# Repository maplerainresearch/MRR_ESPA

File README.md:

# MRR ESPA
## A basic 3D printer control board based on ESP32

This is a bare-minimum 3D printer control board based on the ESP32 microcontroller, which comes with built-in WiFi and BlueTooth.

Current version: v1.3

Get a pre-launch version at our [store](https://www.maplerain.com/en/products).

Facebook [page](https://www.facebook.com/mrrespx/) <br>
Facebook [group](https://www.facebook.com/groups/mrr.espx.users/) (for discussions, etc.)

## Features:
- Able to use up to 4 stepper drivers: X, Y, Z, and E0
- 12V to 24V input power supply
- Separate power supply for the heat bed
- X, Y, and Z min endstops
- Allows the use of a Z-axis probe, such as an inductive sensor, running on the input supply voltage (12V to 24V)
- AUX1 connector for use with an external host, such as the closed-source MKS TFT32 (**Untested!!**)
- Physical size of 99.5mm by 90.5mm. Mounting holes are 3.5mm in diameter, with centers 4mm from the edges.
- "RESET" button can be used to reset the board.

Check out the [Kickstarter page.](https://www.kickstarter.com/projects/maplerainresearch/mrr-espa)

# Firmware

Marlin 2.0 has added support for ESP32. This board was based on the initial pins definition used. <br>
In addition, [Luc](https://github.com/luc-github) has been working on a Marlin fork which incorporates part of his ESP3D webUI into Marlin itself.

## Flashing firmware

- You should be able to flash firmware through the USB port. Depending on your operating system, you may need to install drivers for the CH340. Please use Google or another search engine to find the right CH340 driver for your operating system.
- To flash firmware by directly connecting to TX/RX pins, you will need to connect IO0 to GND, then reboot (press "BOOT" button) to enter flash mode. After flashing the firmware, disconnect IO0 from GND, and press "BOOT" button again to reboot into normal mode.
- Use a baud rate of 115200.
- Once the firmware has been flashed for the first time, further updates can be flashed via OTA.

# Jumpers

- 5V_SEL: Connect to VIN for normal operation; only short (close) this jumper to VUSB if you need to power the board via USB. Note: Powering the board with both PSU and USB may cause unstable operation during heating.
- PWR_SEL: Connect the middle pin PWR_SEL to pin labeled "12V" if using 12V; connect PWR_SEL to pin labeled "24V" if using 24V.
- Stepper driver jumpers:
  - MS1: VIO to set high; SPI if using TMC SPI mode
  - MS2: VIO to set high; SPI if using TMC SPI mode
  - MS3: VIO to set high; SPI if using TMC SPI mode
  - RST: SLP if using A4988/DRV8825; SPI if using TMC SPI mode

# Pins

See separate PIN_DEF.txt file.

# License
Released under CERN Open Hardware Licence v1.2. See LICENSE.txt for details.

## Warning

- This product uses high currents which may cause fires. Use with caution.
- Do not use input voltages higher than 24V. Input current must not exceed 15A.
- Do not attempt to use more than 15A for the heated bed. While the MOSFET is capable of such currents, the connectors are not. If you need more than 15A, use an external MOSFET. In any case, it is highly recommended to use an external MOSFET for the heated bed to avoid drawing high currents through this product.
- If using a current of more than 10A for the heated bed, it is highly recommended to provide active cooling for the board as the MOSFET and adjacent areas can get very hot due to the high current.
- The underside of the board has PCB traces which are exposed for better cooling. These traces may be carrying high currents and can get very hot. DO NOT touch them, and DO NOT allow these traces to come into contact with metal or other conductive materials.
- Do not attempt to use more than 5A for the hot end. While the MOSFET is capable of such currents, the connectors are not. If you need more than 5A, use an external MOSFET.
- Do not reverse polarity.
- The breakout and endstop pins are rated for 3.3V, which is the voltage the ESP32 operates at. Attempting to feed inputs above 3.3V to these pins may damage the board.
- It is recommended to power the board only via USB (i.e. turn off PSU power supply) when flashing the board.

## Disclaimer

This product is provided as-is. While care has been taken to design a safe product, it is the user's responsibility to make sure precautions are taken to prevent damage or injury when using this product. This includes adhering to all warnings provided. By using this product, the user accepts responsibility to bear all liabilities from any damage or injury arising from the use of this product.

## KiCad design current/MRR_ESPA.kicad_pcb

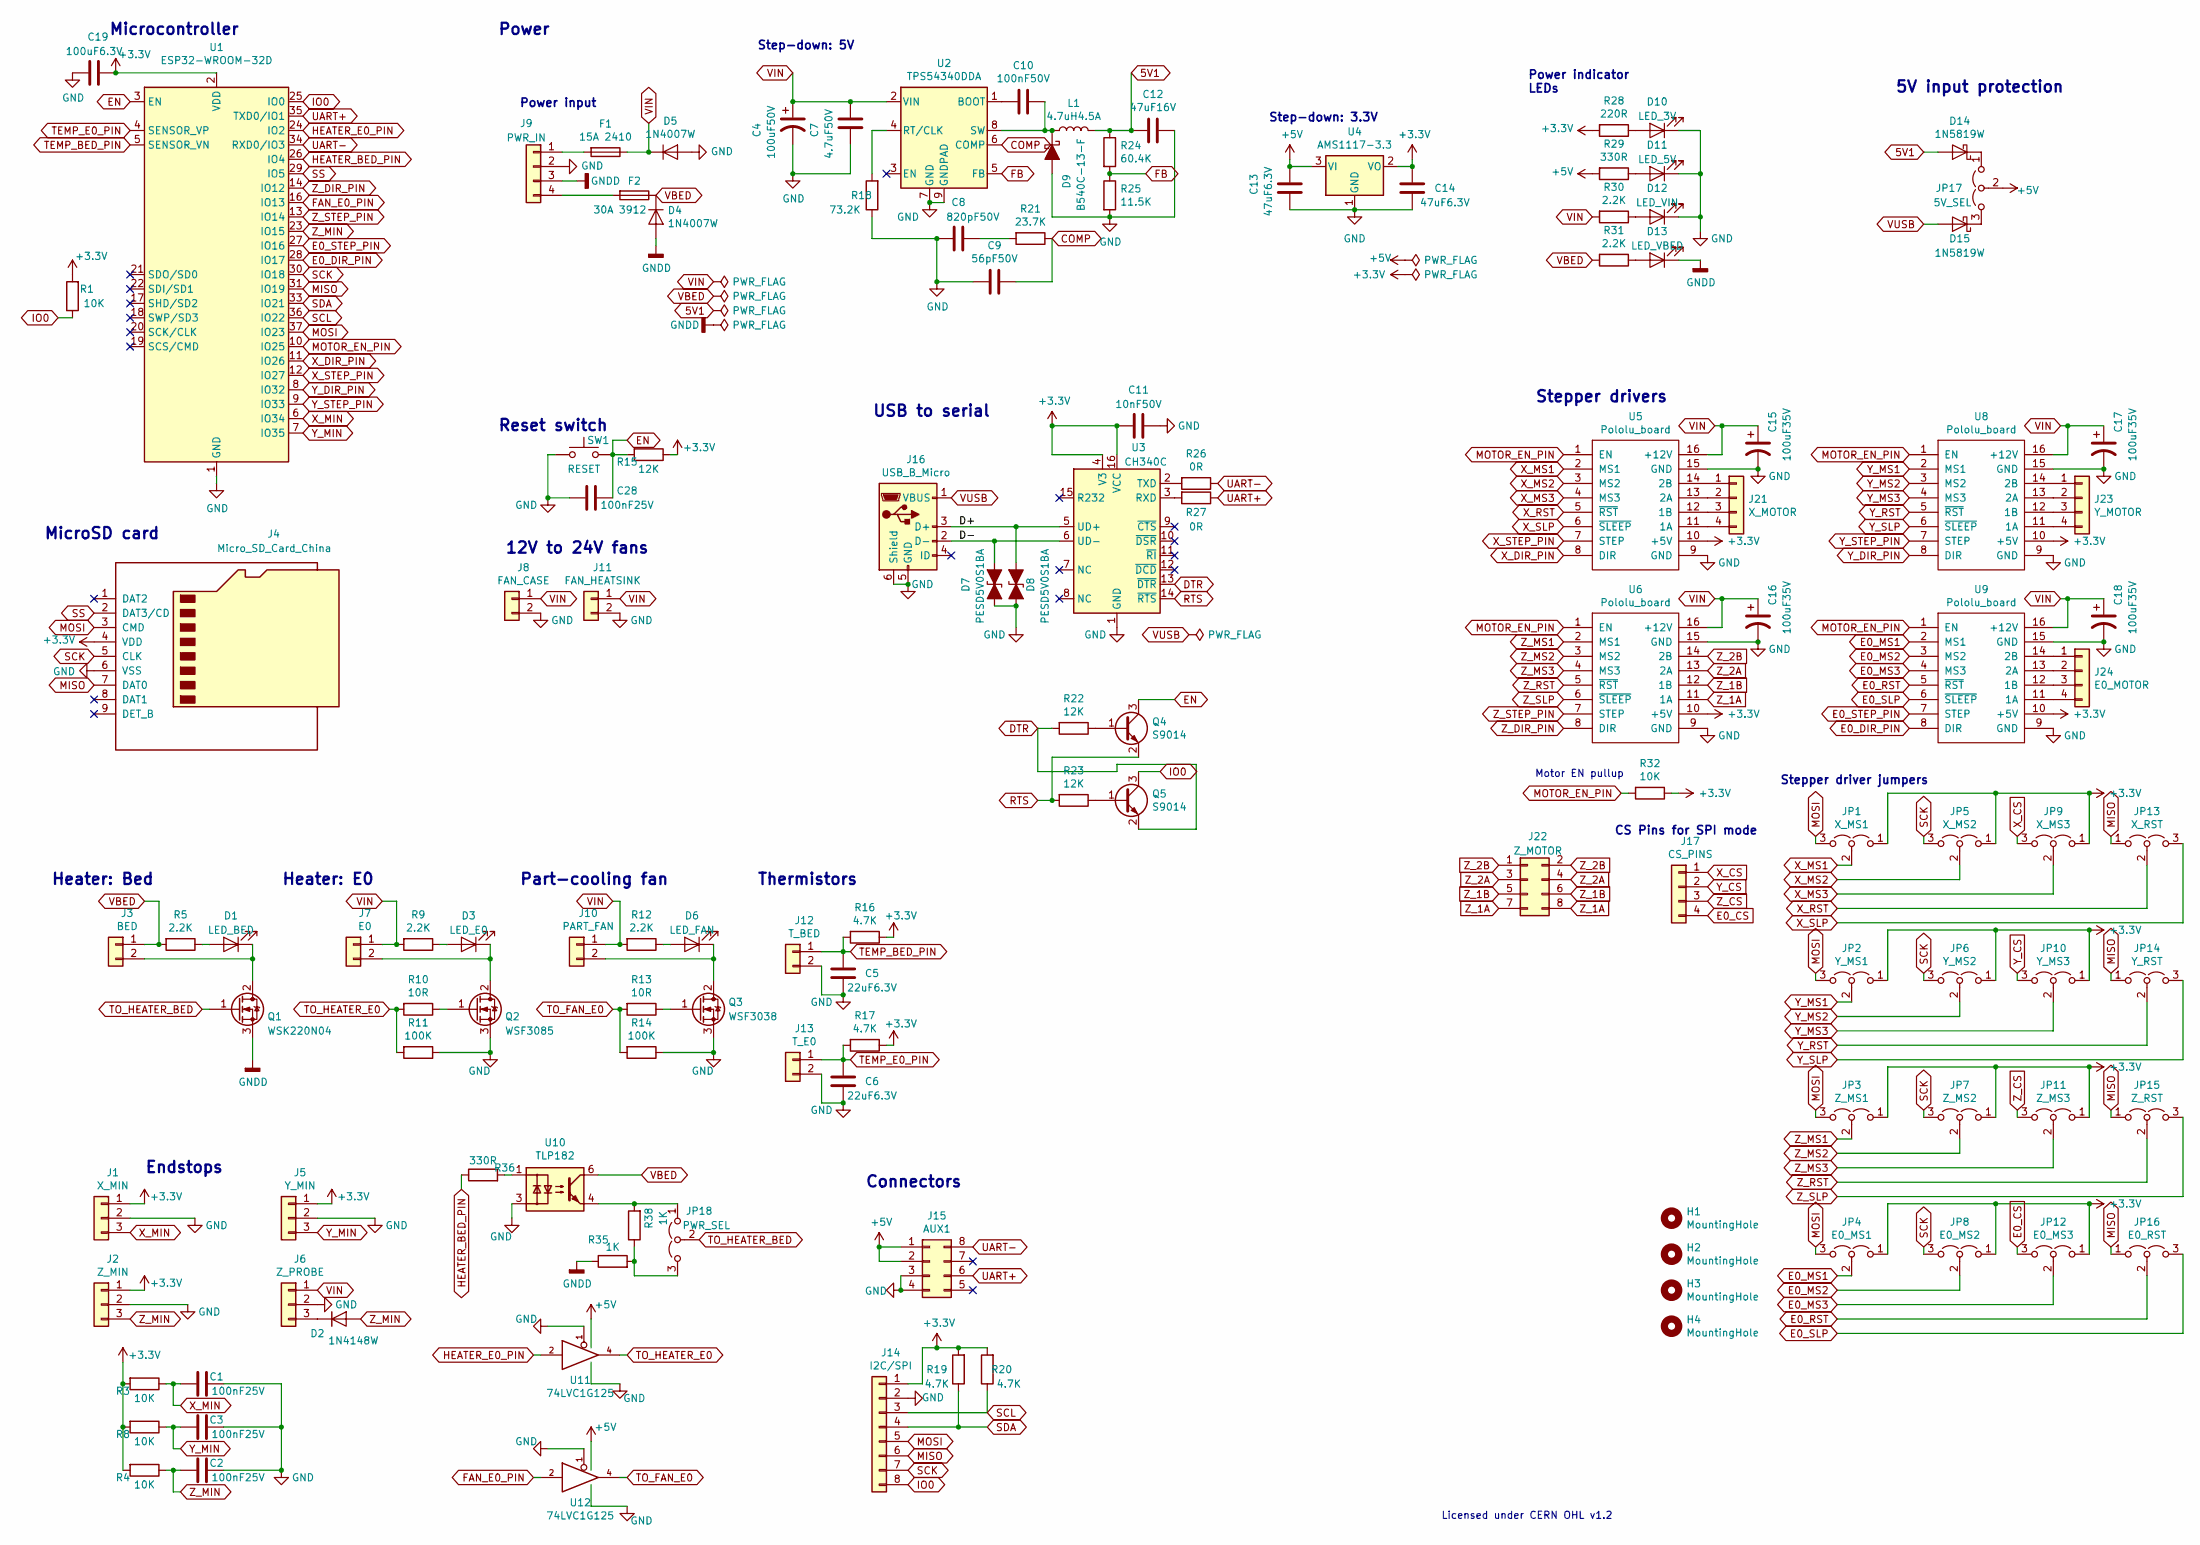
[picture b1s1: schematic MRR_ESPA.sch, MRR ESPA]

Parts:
C1, C2, C3, C28: 100nF25V; C_0805_2012Metric; Mfg part no. 0805B104K250; LCSC Part Number C128353
C4: 100uF50V; CP_Elec_8x10; Mfg part no. VEJ101M1HTR-0810; LCSC Part Number C176665
C5, C6: 22uF6.3V; C_0805_2012Metric; Mfg part no. CL21A226MQQNNNE; LCSC Part Number C5674
C7: 4.7uF50V; C_1206_3216Metric; Mfg part no. CL31B475KBHNFNE; LCSC Part Number C307575
C8: 820pF50V; C_0805_2012Metric; Mfg part no. 0805B821K500CT; LCSC Part Number C152862
C9: 56pF50V; C_0805_2012Metric; Mfg part no. 0805N560J500CT; LCSC Part Number C296102
C10: 100nF50V; C_0805_2012Metric; Mfg part no. GCM21BR71H104KA37L; LCSC Part Number C161260
C11: 10nF50V; C_0805_2012Metric; Mfg part no. 0805B103K500NT; LCSC Part Number C52278
C12: 47uF16V; C_1206_3216Metric; Mfg part no. LMK316BJ476ML-T; LCSC Part Number C92821
C13, C14: 47uF6.3V; C_0805_2012Metric; Mfg part no. JMK212BJ476MG-T; LCSC Part Number C87159
C15, C16, C17, C18: 100uF35V; CP_Elec_6.3x7.7; Mfg part no. CS1V101M-CRE77; LCSC Part Number C97811
C19: 100uF6.3V; C_1206_3216Metric; Mfg part no. CL31A107MQHNNNE; LCSC Part Number C15008
D1: LED_BED; LED_0805; Mfg part no. 17-21SURC/S530-A3/TR8; LCSC Part Number C72037
D2: 1N4148W; D_SOD-123; Mfg part no. 1N4148W; LCSC Part Number C81598
D3: LED_E0; LED_0805; Mfg part no. 17-21SURC/S530-A3/TR8; LCSC Part Number C72037
D4, D5: 1N4007W; D_SOD-123F; Mfg part no. 1N4007W; LCSC Part Number C108803
D6: LED_FAN; LED_0805; Mfg part no. 17-21SURC/S530-A3/TR8; LCSC Part Number C72037
D7, D8: PESD5V0S1BA; D_SOD-323; Mfg part no. PESD5V0S1BA,115; LCSC Part Number C19224
D9: B540C-13-F; D_SMC; Mfg part no. B540C-13-F; LCSC Part Number C72264
D10: LED_3V; LED_0805; Mfg part no. 17-21SYGC/S530-E2/TR8; LCSC Part Number C73548
D11: LED_5V; LED_0805; Mfg part no. 17-21SYGC/S530-E2/TR8; LCSC Part Number C73548
D12: LED_VIN; LED_0805; Mfg part no. 17-21/BHC-XL2M2TY/3T; LCSC Part Number C72035
D13: LED_VBED; LED_0805; Mfg part no. 17-21/BHC-XL2M2TY/3T; LCSC Part Number C72035
D14, D15: 1N5819W; D_SOD-123; Mfg part no. 1N5819W; LCSC Part Number C169540
F1: 15A 2410; Littelfuse_0451; Mfg part no. 0451015.MRL; LCSC Part Number C44480
F2: 30A 3912; Littelfuse_456; Mfg part no. 0456030.ER; LCSC Part Number C187558
H1, H2, H3, H4: MountingHole; MountingHole_3.2mm_M3_DIN965
J1: X_MIN; JST_XH_B03B-XH-A_1x03_P2.50mm_Vertical; Mfg part no. B3B-XH-A(LF)(SN); LCSC Part Number C144394
J2: Z_MIN; JST_XH_B03B-XH-A_1x03_P2.50mm_Vertical; Mfg part no. B3B-XH-A(LF)(SN); LCSC Part Number C144394
J3: BED; TerminalBlock_Phoenix_MKDS-3-2-5.08_1x02_P5.08mm_Horizontal; Mfg part no. MKDS3/2-5.08; LCSC Part Number C89120
J4: Micro_SD_Card_China; Conn_uSDcard; Mfg part no. TF-15×15; LCSC Part Number C111196
J5: Y_MIN; JST_XH_B03B-XH-A_1x03_P2.50mm_Vertical; Mfg part no. B3B-XH-A(LF)(SN); LCSC Part Number C144394
J6: Z_PROBE; JST_XH_B03B-XH-A_1x03_P2.50mm_Vertical; Mfg part no. B3B-XH-A(LF)(SN); LCSC Part Number C144394
J7: E0; TerminalBlock_Phoenix_MKDS-1,5-2-5.08_1x02_P5.08mm_Horizont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; Mfg part no. MKDSN1.5/2-5.08; LCSC Part Number C91153
J8: FAN_CASE; PinHeader_1x02_P2.54mm_Vertical; Mfg part no. C124375; LCSC Part Number C124375
J9: PWR_IN; TerminalBlock_Phoenix_MKDS-3-4-5.08_1x04_P5.08mm_Horizontal; Mfg part no. MKDS3/4-5.08; LCSC Part Number C90087
J10: PART_FAN; PinHeader_1x02_P2.54mm_Vertical; Mfg part no. C124375; LCSC Part Number C124375
J11: FAN_HEATSINK; PinHeader_1x02_P2.54mm_Vertical; Mfg part no. C124375; LCSC Part Number C124375
J12: T_BED; JST_XH_B02B-XH-A_1x02_P2.50mm_Vertical; Mfg part no. B2B-XH-A(LF)(SN); LCSC Part Number C158012
J13: T_E0; JST_XH_B02B-XH-A_1x02_P2.50mm_Vertical; Mfg part no. B2B-XH-A(LF)(SN); LCSC Part Number C158012
J14: I2C/SPI; PinHeader_1x08_P2.54mm_Vertical; Mfg part no. C124381; LCSC Part Number C124381
J15: AUX1; IDC-Header_2x04_P2.54mm_Vertical; Mfg part no. C9135; LCSC Part Number C9135
J16: USB_B_Micro; USB_Micro-B_Molex-105017-0001; Mfg part no. 105017-0001; LCSC Part Number C136000
J17: CS_PINS; PinHeader_1x04_P2.54mm_Vertical; Mfg part no. C124378; LCSC Part Number C124378
J21: X_MOTOR; PinHeader_1x04_P2.54mm_Vertical; Mfg part no. C124378; LCSC Part Number C124378
J22: Z_MOTOR; PinHeader_2x04_P2.54mm_Vertical; Mfg part no. C124386; LCSC Part Number C124386
J23: Y_MOTOR; PinHeader_1x04_P2.54mm_Vertical; Mfg part no. C124378; LCSC Part Number C124378
J24: E0_MOTOR; PinHeader_1x04_P2.54mm_Vertical; Mfg part no. C124378; LCSC Part Number C124378
JP1: X_MS1; PinHeader_1x03_P2.54mm_Vertical; Mfg part no. C124376; LCSC Part Number C124376
JP2: Y_MS1; PinHeader_1x03_P2.54mm_Vertical; Mfg part no. C124376; LCSC Part Number C124376
JP3: Z_MS1; PinHeader_1x03_P2.54mm_Vertical; Mfg part no. C124376; LCSC Part Number C124376
JP4: E0_MS1; PinHeader_1x03_P2.54mm_Vertical; Mfg part no. C124376; LCSC Part Number C124376
JP5: X_MS2; PinHeader_1x03_P2.54mm_Vertical; Mfg part no. C124376; LCSC Part Number C124376
JP6: Y_MS2; PinHeader_1x03_P2.54mm_Vertical; Mfg part no. C124376; LCSC Part Number C124376
JP7: Z_MS2; PinHeader_1x03_P2.54mm_Vertical; Mfg part no. C124376; LCSC Part Number C124376
JP8: E0_MS2; PinHeader_1x03_P2.54mm_Vertical; Mfg part no. C124376; LCSC Part Number C124376
JP9: X_MS3; PinHeader_1x03_P2.54mm_Vertical; Mfg part no. C124376; LCSC Part Number C124376
JP10: Y_MS3; PinHeader_1x03_P2.54mm_Vertical; Mfg part no. C124376; LCSC Part Number C124376
JP11: Z_MS3; PinHeader_1x03_P2.54mm_Vertical; Mfg part no. C124376; LCSC Part Number C124376
JP12: E0_MS3; PinHeader_1x03_P2.54mm_Vertical; Mfg part no. C124376; LCSC Part Number C124376
JP13: X_RST; PinHeader_1x03_P2.54mm_Vertical; Mfg part no. C124376; LCSC Part Number C124376
JP14: Y_RST; PinHeader_1x03_P2.54mm_Vertical; Mfg part no. C124376; LCSC Part Number C124376
JP15: Z_RST; PinHeader_1x03_P2.54mm_Vertical; Mfg part no. C124376; LCSC Part Number C124376
JP16: E0_RST; PinHeader_1x03_P2.54mm_Vertical; Mfg part no. C124376; LCSC Part Number C124376
JP17: 5V_SEL; PinHeader_1x03_P2.54mm_Vertical; Mfg part no. C124376; LCSC Part Number C124376
JP18: PWR_SEL; PinHeader_1x03_P2.54mm_Vertical; Mfg part no. C124376; LCSC Part Number C124376
L1: 4.7uH4.5A; SMMS0530; Mfg part no. SMMS0530-4R7M; LCSC Part Number C181722
Q1: WSK220N04; TO-263-2; Mfg part no. WSK220N04; LCSC Part Number C148446
Q2: WSF3085; TO-252-2; Mfg part no. WSF3085; LCSC Part Number C148428
Q3: WSF3038; TO-252-2; Mfg part no. WSF3038; LCSC Part Number C148426
Q4, Q5: S9014; SOT-23; Mfg part no. S9014; LCSC Part Number C181164
R1, R3, R4, R8, R32: 10K; R_0805_2012Metric; Mfg part no. 0805W8F2201T5E; LCSC Part Number C38522
R5, R9, R12, R30, R31: 2.2K; R_0805_2012Metric; Mfg part no. 0805W8F2201T5E; LCSC Part Number C17520
R10, R13: 10R; R_0805_2012Metric; Mfg part no. 0805W8F100JT5E; LCSC Part Number C17415
R11, R14: 100K; R_0805_2012Metric; Mfg part no. 0805W8F1003T5E; LCSC Part Number C149504
R15, R22, R23: 12K; R_0805_2012Metric; Mfg part no. 0805W8F1202T5E; LCSC Part Number C17444
R16, R17, R19, R20: 4.7K; R_0805_2012Metric; Mfg part no. 0805W8F4701T5E; LCSC Part Number C17673
R18: 73.2K; R_0805_2012Metric; Mfg part no. WR08X7322FTL; LCSC Part Number C170958
R21: 23.7K; R_0805_2012Metric; Mfg part no. WR08X2372FTL; LCSC Part Number C170848
R24: 60.4K; R_0805_2012Metric; Mfg part no. RC0805FR-0760K4L; LCSC Part Number C273994
R25: 11.5K; R_0805_2012Metric; Mfg part no. 0805W8F1152T5E; LCSC Part Number C17418
R26, R27: 0R; R_0805_2012Metric; Mfg part no. 0805W8F0000T5E; LCSC Part Number C17477
R28: 220R; R_0805_2012Metric; Mfg part no. 0805W8F2200T5E; LCSC Part Number C17557
R29, R36: 330R; R_0805_2012Metric; Mfg part no. 0805W8F3300T5E; LCSC Part Number C17630
R35, R38: 1K; R_0805_2012Metric; Mfg part no. 0805W8F1001T5E; LCSC Part Number C17513
SW1: RESET; 6x6mmTactileSwitch; Mfg part no. K2-6639SP-C4SC-04; LCSC Part Number C83206
U1: ESP32-WROOM-32D; ESP32-WROOM-32; Mfg part no. ESP32-WROOM-32; LCSC Part Number C95209
U2: TPS54340DDA; TI_SO-PowerPAD-8_ThermalVias; Mfg part no. TPS54340DDAR; LCSC Part Number C45886
U3: CH340C; SOIC-16_3.9x9.9mm_P1.27mm; Mfg part no. CH340C; LCSC Part Number C84681
U4: AMS1117-3.3; SOT-223-3_TabPin2; Mfg part no. AMS1117-3.3; LCSC Part Number C6186
U5, U6, U8, U9: Pololu_board; Pololu_Breakout-16_15.2x20.3mm; Mfg part no. x2; LCSC Part Number C27438
U10: TLP182; MFSOP6-4_4.4x3.6mm_P1.27mm; Mfg part no. TLP182(GB-TPL,E; LCSC Part Number C96457
U11, U12: 74LVC1G125; SOT-353_SC-70-5; Mfg part no. 74LVC1G125GW,125; LCSC Part Number C12519

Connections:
5V1: C12.2, D14.2 (A), L1.2, R24.1
+3V3: C11.2, C14.1, C19.1, J1.1, J2.1, J4.4 (VDD), J5.1, J14.1, JP1.1 (A), JP2.1 (A), JP3.1 (A), JP4.1 (A), JP5.1 (A), JP6.1 (A), JP7.1 (A), JP8.1 (A), JP9.1 (A), JP10.1 (A), JP11.1 (A), JP12.1 (A), R1.2, R3.2, R4.2, R8.2, R15.1, R16.1, R17.1, R19.2, R20.2, R28.2, R32.1, U1.2 (VDD), U3.4 (V3), U3.16 (VCC), U4.2 (VO), U5.10 (+5V), U6.10 (+5V), U8.10 (+5V), U9.10 (+5V)
+5V: C13.1, J15.1, J15.2, JP17.2 (C), R29.2, U4.3 (VI), U11.5 (VCC), U12.5 (VCC)
/D+: D8.1 (A1), J16.3 (D+), U3.5 (UD+)
/D-: D7.1 (A1), J16.2 (D-), U3.6 (UD-)
COMP: C9.1, R21.1, U2.6 (COMP)
DTR: Q5.2 (E), R22.2, U3.13 (~DTR)
E0_CS: J17.4, JP12.3 (B)
E0_DIR_PIN: U1.28 (IO17), U9.8 (DIR)
E0_MS1: JP4.2 (C), U9.2 (MS1)
E0_MS2: JP8.2 (C), U9.3 (MS2)
E0_MS3: JP12.2 (C), U9.4 (MS3)
E0_RST: JP16.2 (C), U9.5 (~RST)
E0_SLP: JP16.3 (B), U9.6 (~SLEEP)
E0_STEP_PIN: U1.27 (IO16), U9.7 (STEP)
EN: C28.1, Q4.3 (C), R15.2, SW1.2, U1.3 (EN)
FAN_E0_PIN: U1.16 (IO13), U12.2
FB: R24.2, R25.1, U2.5 (FB)
GND: C1.1, C2.1, C3.1, C4.2, C5.1, C6.1, C7.1, C8.2, C9.2, C11.1, C12.1, C13.2, C14.2, C15.2, C16.2, C17.2, C18.2, C19.2, C28.2, D5.2 (A), D7.2 (A2), D8.2 (A2), D9.2 (A), D10.1 (K), D11.1 (K), D12.1 (K), J1.2, J2.2, J4.6 (VSS), J5.2, J6.2, J8.2, J9.2, J11.2, J12.2, J13.2, J14.2, J15.3, J15.4, J16.5 (GND), J16.6 (Shield), Q2.3 (S), Q3.3 (S), R11.1, R14.1, R18.1, R25.2, SW1.1, U1.1 (GND), U1.15 (GND), U1.38 (GND), U1.39, U2.7 (GND), U2.9 (GNDPAD), U3.1 (GND), U4.1 (GND), U5.9 (GND), U5.15 (GND), U6.9 (GND), U6.15 (GND), U8.9 (GND), U8.15 (GND), U9.9 (GND), U9.15 (GND), U10.3, U11.1, U11.3 (GND), U12.1, U12.3 (GND)
GNDD: D4.2 (A), D13.1 (K), J9.3, Q1.3 (S), R35.1
HEATER_BED_PIN: R36.1, U1.26 (IO4)
HEATER_E0_PIN: U1.24 (IO2), U11.2
IO0: J14.8, Q5.3 (C), R1.1, U1.25 (IO0)
MISO: J4.7 (DAT0), J14.6, JP13.1 (A), JP14.1 (A), JP15.1 (A), JP16.1 (A), U1.31 (IO19)
MOSI: J4.3 (CMD), J14.5, JP1.3 (B), JP2.3 (B), JP3.3 (B), JP4.3 (B), U1.37 (IO23)
MOTOR_EN_PIN: R32.2, U1.10 (IO25), U5.1 (EN), U6.1 (EN), U8.1 (EN), U9.1 (EN)
unnamed: C8.1, R21.2
unnamed: C10.1, D9.1 (K), L1.1, U2.8 (SW)
unnamed: C10.2, U2.1 (BOOT)
unnamed: D1.1 (K), J3.2, Q1.2 (D)
unnamed: D1.2 (A), R5.1
unnamed: D2.1 (K), J6.3
unnamed: D3.1 (K), J7.2, Q2.2 (D)
unnamed: D3.2 (A), R9.1
unnamed: D6.1 (K), J10.2, Q3.2 (D)
unnamed: D6.2 (A), R12.1
unnamed: D10.2 (A), R28.1
unnamed: D11.2 (A), R29.1
unnamed: D12.2 (A), R30.1
unnamed: D13.2 (A), R31.1
unnamed: D14.1 (K), JP17.1 (A)
unnamed: D15.1 (K), JP17.3 (B)
unnamed: F1.2, J9.1
unnamed: F2.2, J9.4
unnamed: J21.1, U5.14 (2B)
unnamed: J21.2, U5.13 (2A)
unnamed: J21.3, U5.12 (1B)
unnamed: J21.4, U5.11 (1A)
unnamed: J23.1, U8.14 (2B)
unnamed: J23.2, U8.13 (2A)
unnamed: J23.3, U8.12 (1B)
unnamed: J23.4, U8.11 (1A)
unnamed: J24.1, U9.14 (2B)
unnamed: J24.2, U9.13 (2A)
unnamed: J24.3, U9.12 (1B)
unnamed: J24.4, U9.11 (1A)
unnamed: JP18.1 (A), R38.2, U10.4
unnamed: JP18.3 (B), R35.2, R38.1
unnamed: Q2.1 (G), R10.1
unnamed: Q3.1 (G), R13.1
unnamed: Q4.1 (B), R22.1
unnamed: Q5.1 (B), R23.1
unnamed: R18.2, U2.4 (RT/CLK)
unnamed: R26.2, U3.2 (TXD)
unnamed: R27.2, U3.3 (RXD)
unnamed: R36.2, U10.1
RTS: Q4.2 (E), R23.2, U3.14 (~RTS)
SCK: J4.5 (CLK), J14.7, JP5.3 (B), JP6.3 (B), JP7.3 (B), JP8.3 (B), U1.30 (IO18)
SCL: J14.3, R20.1, U1.36 (IO22)
SDA: J14.4, R19.1, U1.33 (IO21)
SS: J4.2 (DAT3/CD), U1.29 (IO5)
TEMP_BED_PIN: C5.2, J12.1, R16.2, U1.5 (SENSOR_VN)
TEMP_E0_PIN: C6.2, J13.1, R17.2, U1.4 (SENSOR_VP)
TO_FAN_E0: R13.2, R14.2, U12.4
TO_HEATER_BED: JP18.2 (C), Q1.1 (G)
TO_HEATER_E0: R10.2, R11.2, U11.4
UART+: J15.6, R27.1, U1.35 (TXD0/IO1)
UART-: J15.8, R26.1, U1.34 (RXD0/IO3)
VBED: D4.1 (K), F2.1, J3.1, R5.2, R31.2, U10.6
VIN: C4.1, C7.2, C15.1, C16.1, C17.1, C18.1, D5.1 (K), F1.1, J6.1, J7.1, J8.1, J10.1, J11.1, R9.2, R12.2, R30.2, U2.2 (VIN), U5.16 (+12V), U6.16 (+12V), U8.16 (+12V), U9.16 (+12V)
VUSB: D15.2 (A), J16.1 (VBUS)
X_CS: J17.1, JP9.3 (B)
X_DIR_PIN: U1.11 (IO26), U5.8 (DIR)
X_MIN: C1.2, J1.3, R3.1, U1.6 (IO34)
X_MS1: JP1.2 (C), U5.2 (MS1)
X_MS2: JP5.2 (C), U5.3 (MS2)
X_MS3: JP9.2 (C), U5.4 (MS3)
X_RST: JP13.2 (C), U5.5 (~RST)
X_SLP: JP13.3 (B), U5.6 (~SLEEP)
X_STEP_PIN: U1.12 (IO27), U5.7 (STEP)
Y_CS: J17.2, JP10.3 (B)
Y_DIR_PIN: U1.8 (IO32), U8.8 (DIR)
Y_MIN: C3.2, J5.3, R8.1, U1.7 (IO35)
Y_MS1: JP2.2 (C), U8.2 (MS1)
Y_MS2: JP6.2 (C), U8.3 (MS2)
Y_MS3: JP10.2 (C), U8.4 (MS3)
Y_RST: JP14.2 (C), U8.5 (~RST)
Y_SLP: JP14.3 (B), U8.6 (~SLEEP)
Y_STEP_PIN: U1.9 (IO33), U8.7 (STEP)
Z_1A: J22.7, J22.8, U6.11 (1A)
Z_1B: J22.5, J22.6, U6.12 (1B)
Z_2A: J22.3, J22.4, U6.13 (2A)
Z_2B: J22.1, J22.2, U6.14 (2B)
Z_CS: J17.3, JP11.3 (B)
Z_DIR_PIN: U1.14 (IO12), U6.8 (DIR)
Z_MIN: C2.2, D2.2 (A), J2.3, R4.1, U1.23 (IO15)
Z_MS1: JP3.2 (C), U6.2 (MS1)
Z_MS2: JP7.2 (C), U6.3 (MS2)
Z_MS3: JP11.2 (C), U6.4 (MS3)
Z_RST: JP15.2 (C), U6.5 (~RST)
Z_SLP: JP15.3 (B), U6.6 (~SLEEP)
Z_STEP_PIN: U1.13 (IO14), U6.7 (STEP)

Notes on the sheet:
Microcontroller
MicroSD card
Power
Step-down: 5V
Step-down: 3.3V
Power indicator LEDs
Power input
USB to serial
5V input protection
Heater: Bed
Heater: E0
Part-cooling fan
Motor EN pullup
Stepper drivers
12V to 24V fans
Thermistors
Endstops
Reset switch
Connectors
Stepper driver jumpers
Licensed under CERN OHL v1.2
CS Pins for SPI mode

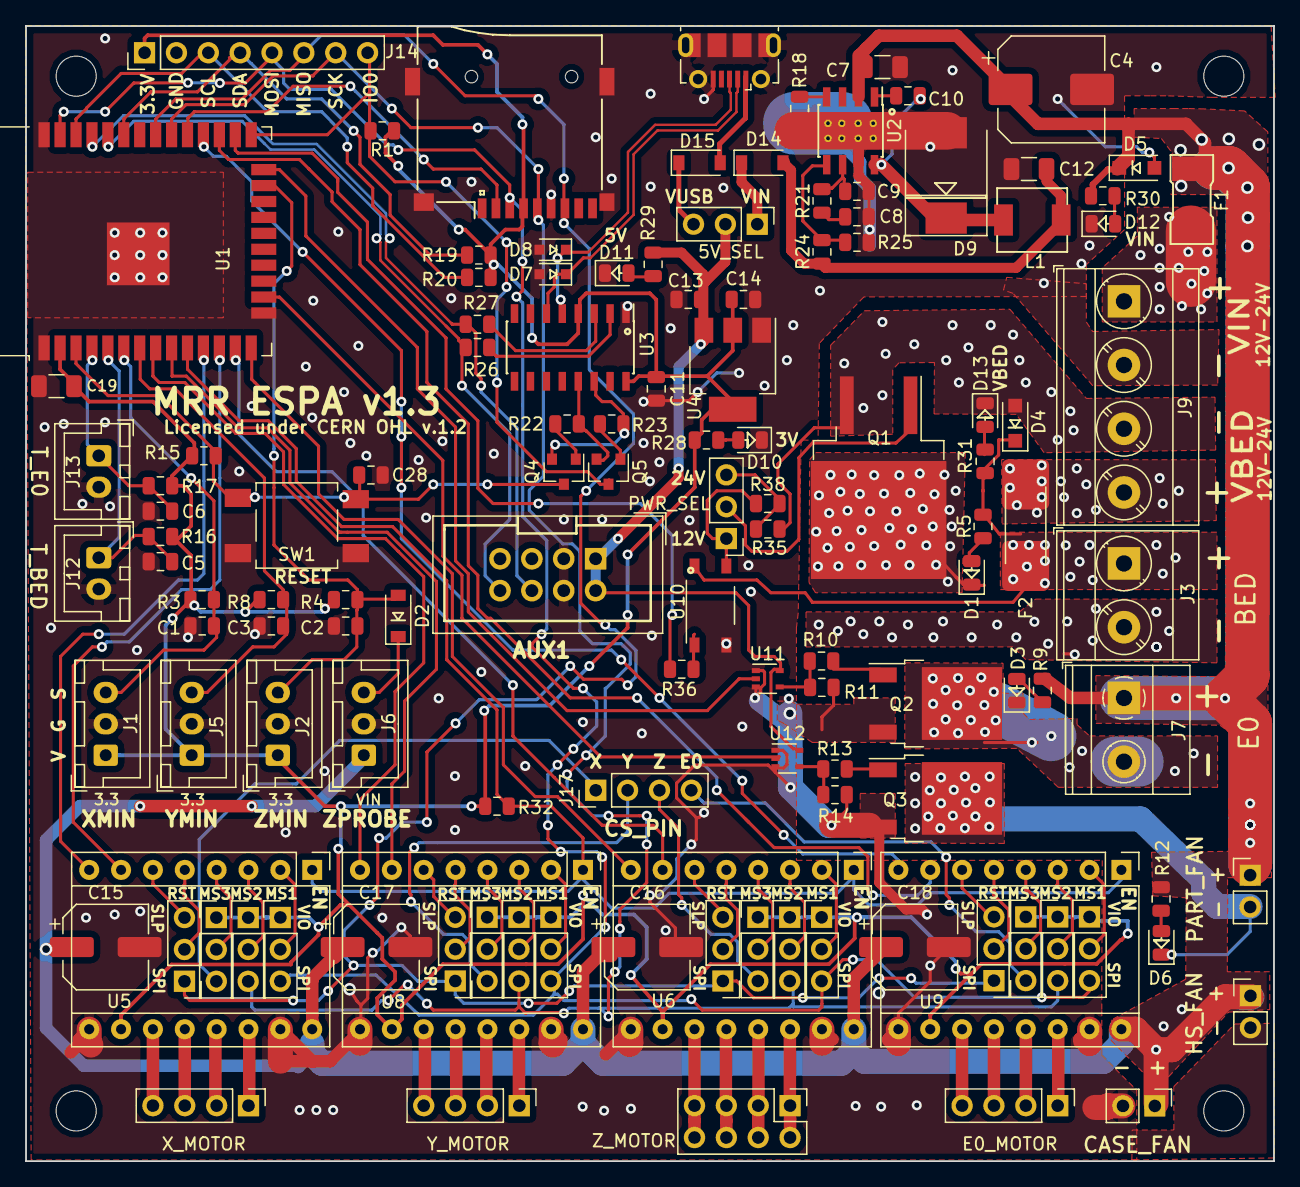
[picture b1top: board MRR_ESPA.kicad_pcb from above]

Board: 2 copper layers, 99.5 x 90.5 mm, 130 parts (0 on the bottom side), 112 nets.

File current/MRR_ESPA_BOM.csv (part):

Reference, Value, Footprint, Datasheet, LCSC Part Number, Manufacturer, Mfg part no.
"U1","ESP32-WROOM-32D","RF_Module:ESP32-WROOM-32","https://www.espressif.com/sites/default/files/documentation/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","C95209","Espressif Systems","ESP32-WROOM-32"
"J9","PWR_IN","TerminalBlock_Phoenix:TerminalBlock_Phoenix_MKDS-3-4-5.08_1x04_P5.08mm_Horizontal","~","C90087","Phoenix Contact","MKDS3/4-5.08"
"F1","15A 2410","projfp:Littelfuse_0451","Bel 0679H9150-01","C44480","Littelfuse","0451015.MRL"
"F2","30A 3912","projfp:Littelfuse_456","Bel 0678H9300-02","C187558","Littelfuse","0456030.ER"
"D4","1N4007W","projfp:D_SOD-123F","http://www.vishay.com/docs/88503/1n4001.pdf","C108803","Shandong Jingdao Microelectronics","1N4007W"
"D5","1N4007W","projfp:D_SOD-123F","http://www.vishay.com/docs/88503/1n4001.pdf","C108803","Shandong Jingdao Microelectronics","1N4007W"
"U2","TPS54340DDA","Package_SO:TI_SO-PowerPAD-8_ThermalVias","http://www.ti.com/lit/ds/symlink/tps54340.pdf","C45886","Texas Instruments","TPS54340DDAR"
"C10","100nF50V","Capacitor_SMD:C_0805_2012Metric","~","C161260","Murata Electronics","GCM21BR71H104KA37L"
"C7","4.7uF50V","Capacitor_SMD:C_1206_3216Metric","~","C307575","Samsung Electro-Mechanics","CL31B475KBHNFNE"
"C4","100uF50V","Capacitor_SMD:CP_Elec_8x10","~","C176665","Lelon","VEJ101M1HTR-0810"
"L1","4.7uH4.5A","projfp:SMMS0530","~","C181722","Shun Xiang Nuo Elec","SMMS0530-4R7M"
"D9","B540C-13-F","projfp:D_SMC","~","C72264","Diodes Incorporated","B540C-13-F"
"R24","60.4K","Resistor_SMD:R_0805_2012Metric","~","C273994","YAGEO","RC0805FR-0760K4L"
"R25","11.5K","Resistor_SMD:R_0805_2012Metric","~","C17418","Uniroyal Elec","0805W8F1152T5E"
"C12","47uF16V","Capacitor_SMD:C_1206_3216Metric","~","C92821","Taiyo Yuden","LMK316BJ476ML-T"
"C8","820pF50V","Capacitor_SMD:C_0805_2012Metric","~","C152862","Walsin Tech Corp","0805B821K500CT"
"R21","23.7K","Resistor_SMD:R_0805_2012Metric","~","C170848","Walsin Tech Corp","WR08X2372FTL"
"C9","56pF50V","Capacitor_SMD:C_0805_2012Metric","~","C296102","Walsin Tech Corp","0805N560J500CT"
"R18","73.2K","Resistor_SMD:R_0805_2012Metric","~","C170958","Walsin Tech Corp","WR08X7322FTL"
"U4","AMS1117-3.3","Package_TO_SOT_SMD:SOT-223-3_TabPin2","http://www.advanced-monolithic.com/pdf/ds1117.pdf","C6186","Advanced Monolithic Systems","AMS1117-3.3"
"C14","47uF6.3V","Capacitor_SMD:C_0805_2012Metric","~","C87159","Taiyo Yuden","JMK212BJ476MG-T"
"C13","47uF6.3V","Capacitor_SMD:C_0805_2012Metric","~","C87159","Taiyo Yuden","JMK212BJ476MG-T"
"R28","220R","Resistor_SMD:R_0805_2012Metric","~","C17557","Uniroyal Elec","0805W8F2200T5E"
"D10","LED_3V","projfp:LED_0805","~","C73548","Everlight Elec","17-21SYGC/S530-E2/TR8"
"R29","330R","Resistor_SMD:R_0805_2012Metric","~","C17630","Uniroyal Elec","0805W8F3300T5E"
"R30","2.2K","Resistor_SMD:R_0805_2012Metric","~","C17520","Uniroyal Elec","0805W8F2201T5E"
"R31","2.2K","Resistor_SMD:R_0805_2012Metric","~","C17520","Uniroyal Elec","0805W8F2201T5E"
"D11","LED_5V","projfp:LED_0805","~","C73548","Everlight Elec","17-21SYGC/S530-E2/TR8"
"D12","LED_VIN","projfp:LED_0805","~","C72035","Everlight Elec","17-21/BHC-XL2M2TY/3T"
"D13","LED_VBED","projfp:LED_0805","~","C72035","Everlight Elec","17-21/BHC-XL2M2TY/3T"
"R26","0R","Resistor_SMD:R_0805_2012Metric","~","C17477","Uniroyal Elec","0805W8F0000T5E"
"R27","0R","Resistor_SMD:R_0805_2012Metric","~","C17477","Uniroyal Elec","0805W8F0000T5E"
"C11","10nF50V","Capacitor_SMD:C_0805_2012Metric","~","C52278","Guangdong Fenghua Advanced Tech","0805B103K500NT"
"J16","USB_B_Micro","Connector_USB:USB_Micro-B_Molex-105017-0001","~","C136000","MOLEX","105017-0001"
"D7","PESD5V0S1BA","projfp:D_SOD-323","~","C19224","Nexperia","PESD5V0S1BA,115"
"D8","PESD5V0S1BA","projfp:D_SOD-323","~","C19224","Nexperia","PESD5V0S1BA,115"
"Q4","S9014","Package_TO_SOT_SMD:SOT-23","http://www.onsemi.com/pub_link/Collateral/2N3055-D.PDF","C181164","Guangdong Hottech","S9014"
"Q5","S9014","Package_TO_SOT_SMD:SOT-23","http://www.onsemi.com/pub_link/Collateral/2N3055-D.PDF","C181164","Guangdong Hottech","S9014"
"R22","12K","Resistor_SMD:R_0805_2012Metric","~","C17444","Uniroyal Elec","0805W8F1202T5E"
"R23","12K","Resistor_SMD:R_0805_2012Metric","~","C17444","Uniroyal Elec","0805W8F1202T5E"
"Q1","WSK220N04","Package_TO_SOT_SMD:TO-263-2","~","C148446","Winsok Semicon","WSK220N04"
"Q2","WSF3085","Package_TO_SOT_SMD:TO-252-2","~","C148428","Winsok Semicon","WSF3085"
"Q3","WSF3038","Package_TO_SOT_SMD:TO-252-2","~","C148426","Winsok Semicon","WSF3038"
"R5","2.2K","Resistor_SMD:R_0805_2012Metric","~","C17520","Uniroyal Elec","0805W8F2201T5E"
"D1","LED_BED","projfp:LED_0805","~","C72037","Everlight Elec","17-21SURC/S530-A3/TR8"
"J3","BED","TerminalBlock_Phoenix:TerminalBlock_Phoenix_MKDS-3-2-5.08_1x02_P5.08mm_Horizontal","~","C89120","Phoenix Contact","MKDS3/2-5.08"
"R9","2.2K","Resistor_SMD:R_0805_2012Metric","~","C17520","Uniroyal Elec","0805W8F2201T5E"
"J7","E0","TerminalBlock_Phoenix:TerminalBlock_Phoenix_MKDS-1,5-2-5.08_1x02_P5.08mm_Horizontal","~","C91153","Phoenix Contact","MKDSN1.5/2-5.08"
"R10","10R","Resistor_SMD:R_0805_2012Metric","~","C17415","Uniroyal Elec","0805W8F100JT5E"
"R11","100K","Resistor_SMD:R_0805_2012Metric","~","C149504","Uniroyal Elec","0805W8F1003T5E"
"R12","2.2K","Resistor_SMD:R_0805_2012Metric","~","C17520","Uniroyal Elec","0805W8F2201T5E"
"R13","10R","Resistor_SMD:R_0805_2012Metric","~","C17415","Uniroyal Elec","0805W8F100JT5E"
"R14","100K","Resistor_SMD:R_0805_2012Metric","~","C149504","Uniroyal Elec","0805W8F1003T5E"
"J10","PART_FAN","Connector_PinHeader_2.54mm:PinHeader_1x02_P2.54mm_Vertical","~","C124375","Shenzhen Cankemeng","C124375"
"U8","Pololu_board","Module:Pololu_Breakout-16_15.2x20.3mm","","C27438","Boom Precision Elec","x2"
"U5","Pololu_board","Module:Pololu_Breakout-16_15.2x20.3mm","","C27438","Boom Precision Elec","x2"
"J21","X_MOTOR","Connector_PinHeader_2.54mm:PinHeader_1x04_P2.54mm_Vertical","~","C124378","Shenzhen Cankemeng","C124378"
"C15","100uF35V","Capacitor_SMD:CP_Elec_6.3x7.7","~","C97811","Semtech","CS1V101M-CRE77"
"U6","Pololu_board","Module:Pololu_Breakout-16_15.2x20.3mm","","C27438","Boom Precision Elec","x2"
"U9","Pololu_board","Module:Pololu_Breakout-16_15.2x20.3mm","","C27438","Boom Precision Elec","x2"
"R32","10K","Resistor_SMD:R_0805_2012Metric","~","C38522","Uniroyal Elec","0805W8F2201T5E"
"J11","FAN_HEATSINK","Connector_PinHeader_2.54mm:PinHeader_1x02_P2.54mm_Vertical","~","C124375","Shenzhen Cankemeng","C124375"
"C16","100uF35V","Capacitor_SMD:CP_Elec_6.3x7.7","~","C97811","Semtech","CS1V101M-CRE77"
"C17","100uF35V","Capacitor_SMD:CP_Elec_6.3x7.7","~","C97811","Semtech","CS1V101M-CRE77"
"C18","100uF35V","Capacitor_SMD:CP_Elec_6.3x7.7","~","C97811","Semtech","CS1V101M-CRE77"
"J23","Y_MOTOR","Connector_PinHeader_2.54mm:PinHeader_1x04_P2.54mm_Vertical","~","C124378","Shenzhen Cankemeng","C124378"
"J24","E0_MOTOR","Connector_PinHeader_2.54mm:PinHeader_1x04_P2.54mm_Vertical","~","C124378","Shenzhen Cankemeng","C124378"
"J22","Z_MOTOR","Connector_PinHeader_2.54mm:PinHeader_2x04_P2.54mm_Vertical","~","C124386","Shenzhen Cankemeng","C124386"
"D3","LED_E0","projfp:LED_0805","~","C72037","Everlight Elec","17-21SURC/S530-A3/TR8"
"D6","LED_FAN","projfp:LED_0805","~","C72037","Everlight Elec","17-21SURC/S530-A3/TR8"
"J8","FAN_CASE","Connector_PinHeader_2.54mm:PinHeader_1x02_P2.54mm_Vertical","~","C124375","Shenzhen Cankemeng","C124375"
"J12","T_BED","Connector_JST:JST_XH_B02B-XH-A_1x02_P2.50mm_Vertical","~","C158012","JST Sales America","B2B-XH-A(LF)(SN)"
"R16","4.7K","Resistor_SMD:R_0805_2012Metric","~","C17673","Uniroyal Elec","0805W8F4701T5E"
"C5","22uF6.3V","Capacitor_SMD:C_0805_2012Metric","~","C5674","Samsung Electro-Mechanics","CL21A226MQQNNNE"
"J13","T_E0","Connector_JST:JST_XH_B02B-XH-A_1x02_P2.50mm_Vertical","~","C158012","JST Sales America","B2B-XH-A(LF)(SN)"
"R17","4.7K","Resistor_SMD:R_0805_2012Metric","~","C17673","Uniroyal Elec","0805W8F4701T5E"
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
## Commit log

2019-06-23 Initial commit to new repo
2019-06-23 Added firmware folder
2019-09-09 Added v1.2
2019-09-19 Added photos
2019-09-22 Added Kickstarter link
2019-10-24 Added v1.3 files
2019-10-24 Added media files
2019-10-25 Added cases
2019-10-30 Updated PRODUCT.txt
2019-11-12 Updated purchase details
2019-11-13 Added dimensions drawing
2019-11-25 Added new photos
2019-12-09 Changed AUX1 connector symbol
2020-01-14 Updated manual
